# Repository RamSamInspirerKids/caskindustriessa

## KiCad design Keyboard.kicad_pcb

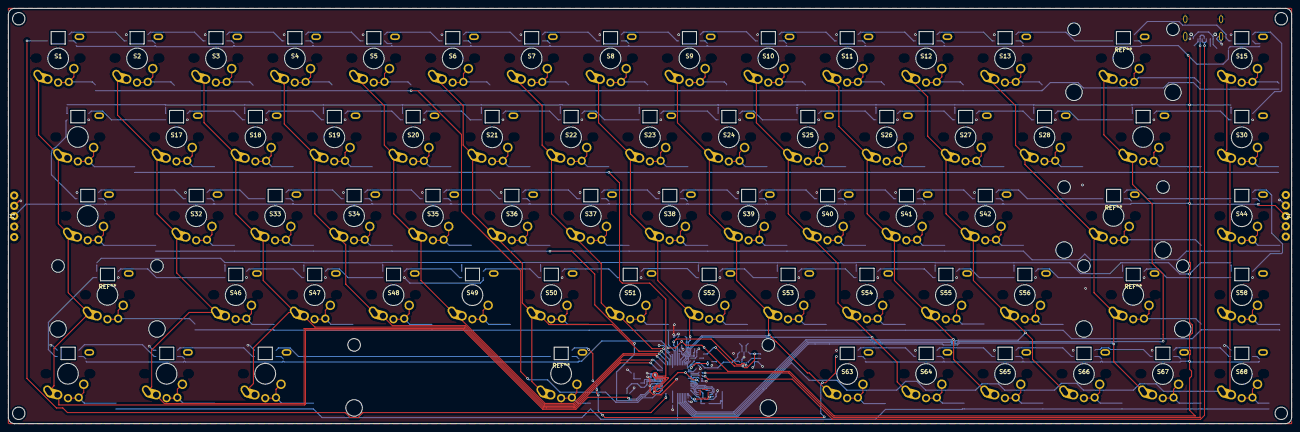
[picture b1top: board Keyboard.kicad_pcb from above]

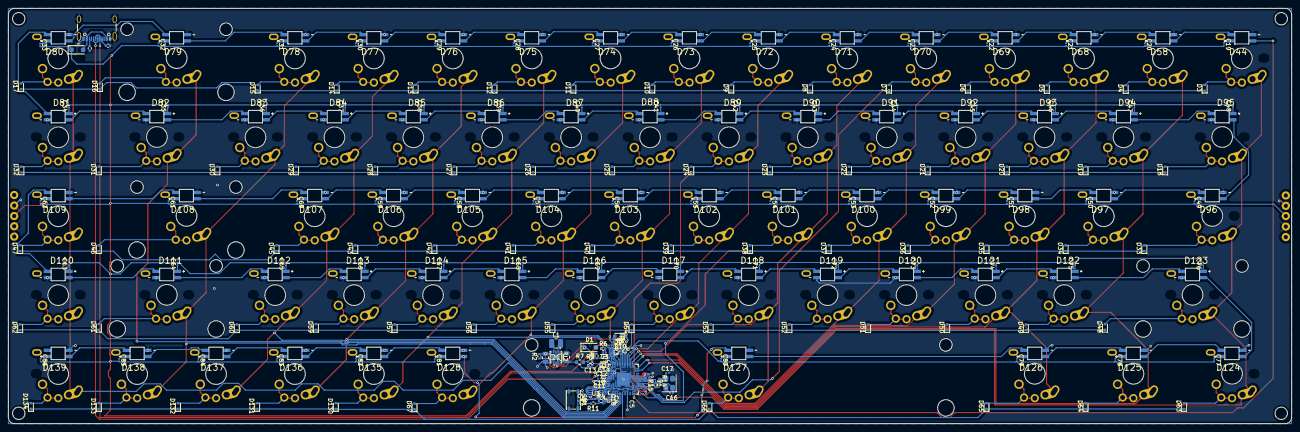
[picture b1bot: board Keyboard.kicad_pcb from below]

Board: 2 copper layers, 309.8 x 100.2 mm, 320 parts (250 on the bottom side), 257 nets.

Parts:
C1, C2: 47u; C_0805_2012Metric
C3: 1n; C_0201_0603Metric
C4, C5, C6, C7, C8, C9, C10, C11, C15: 100n; C_0201_0603Metric
C12, C13, C14, C18: 2u2; C_0402_1005Metric
C16, C17: 15p; C_0201_0603Metric
C19, C20, C21, C22, C23, C24, C25, C26, C27, C28, C29, C30, C31, C32, C33, C34, C35, C36, C37, C38, C39, C40, C41, C42, C43, C44, C45, C46, C47, C48, C49, C50, C51, C52, C53, C54, C55, C56, C57, C58, C59, C60, C61, C62, C63, C64, C65, C66, C67, C68, C69, C70, C71, C72, C73, C74, C75, C76, C77, C78, C79, C80, C81, C82, C83, C84, C85, C86: C0603X5R1A104M030BC; C_0201_0603Metric
D1, D129: MBR1020VL_R1_00001; D_SOD-123F
D2: LTST-C191KGKT; LED_0603_1608Metric
D3, D4, D5, D6, D7, D8, D9, D10, D11, D12, D13, D14, D15, D16, D17, D18, D19, D20, D21, D22, D23, D24, D25, D26, D27, D28, D29, D30, D31, D32, D33, D34, D35, D36, D37, D38, D39, D40, D41, D42, D43, D45, D46, D47, D48, D49, D50, D51, D52, D53, D54, D55, D56, D57, D59, D60, D61, D62, D63, D64, D65, D66, D67, D130, D131, D132, D133, D134: Diode; D_SOD-523
D44, D58, D68, D69, D70, D71, D72, D73, D74, D75, D76, D77, D78, D79, D80, D81, D82, D83, D84, D85, D86, D87, D88, D89, D90, D91, D92, D93, D94, D95, D96, D97, D98, D99, D100, D101, D102, D103, D104, D105, D106, D107, D108, D109, D110, D111, D112, D113, D114, D115, D116, D117, D118, D119, D120, D121, D122, D123, D124, D125, D126, D127, D128, D135, D136, D137, D138, D139: SK6812-E; LED_SK6812-E
J1, J4: Conn_01x05_Socket; Female Connector Pogo 5
J3: USB_C_Receptacle_USB2.0_16P; USB_C_Receptacle_GCT_USB4105-xx-A_16P_TopMnt_Horizontal
L1: SRN2512-2R2M; L_1008_2520Metric
Q1: DMG1012T-7; SOT-523
R1: 10k; R_0402_1005Metric
R2, R6, R8: 100k; R_0402_1005Metric
R3: 470R; R_0402_1005Metric
R4, R15: NO-FIT; R_0402_1005Metric
R5: 200k; R_0402_1005Metric
R7: 200R; R_0603_1608Metric
R9: 1R; R_0402_1005Metric
R10: 5k6; R_0402_1005Metric
R11, R14: 1k; R_0402_1005Metric
R12, R13: 27R; R_0201_0603Metric
R16, R17: 5k1; R_0402_1005Metric
S1, S2, S3, S4, S5, S6, S7, S8, S9, S10, S11, S12, S13, S15, S17, S18, S19, S20, S21, S22, S23, S24, S25, S26, S27, S28, S30, S32, S33, S34, S35, S36, S37, S38, S39, S40, S41, S42, S44, S46, S47, S48, S49, S50, S51, S52, S53, S54, S55, S56, S58, S63, S64, S65, S66, S67, S68: Keyswitch; 1.00U Keyswitch
S14: Keyswitch; 2.00U Keyswitch
S16, S29: Keyswitch; 1.50U Keyswitch
S31, S57: Keyswitch; 1.75U Keyswitch
S43, S45: Keyswitch; 2.25U Keyswitch
S59, S60, S61: Keyswitch; 1.25U Keyswitch
S62: Keyswitch; 6.25U Keyswitch
SW1: PTS810 SJK 250 SMTR LFS; SW_SPST_PTS810
U1: RP2040; QFN-56-1EP_7x7mm_P0.4mm_EP3.2x3.2mm
U2: RT6150B-33GQW; DFN-10-1EP_2.6x2.6mm_P0.5mm_EP1.3x2.2mm
U3: W25Q16JVUXIQ; SON50P300X200X60-9N
Y1: ECS-120-8-33-JGN-TR; Crystal_SMD_SeikoEpson_FA238-4Pin_3.2x2.5mm

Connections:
+1V1: C9.1, C11.1, C12.1, U1.23 (DVDD), U1.45 (VREG_VOUT), U1.50 (DVDD)
+3V3: C2.1, C4.1, C5.1, C6.1, C7.1, C8.1, C10.1, C14.1, C15.1, C18.1, Q1.1 (G), R4.2, R7.1, U1.1 (IOVDD), U1.10 (IOVDD), U1.22 (IOVDD), U1.33 (IOVDD), U1.42 (IOVDD), U1.44 (VREG_IN), U1.48 (USB_VDD), U1.49 (IOVDD), U2.1 (VOUT), U2.10 (FB), U3.8 (VCC)
/3V3_EN: R2.1, U2.6 (EN)
/RP2040/USB_DMX: R13.2, U1.46 (USB_DM)
/RP2040/USB_DPX: R12.2, U1.47 (USB_DP)
/XR: C17.1, R14.1, Y1.3
ADC_AVDD: C13.1, R9.2, U1.43 (ADC_AVDD)
ADC_VREF: R7.2, R9.1
GND: C1.2, C2.2, C3.2, C4.2, C5.2, C6.2, C7.2, C8.2, C9.2, C10.2, C11.2, C12.2, C13.2, C14.2, C15.2, C16.2, C17.2, C18.2, D2.1 (K), D44.3 (GND), D58.3 (GND), D68.3 (GND), D69.3 (GND), D70.3 (GND), D71.3 (GND), D72.3 (GND), D73.3 (GND), D74.3 (GND), D75.3 (GND), D76.3 (GND), D77.3 (GND), D78.3 (GND), D79.3 (GND), D80.3 (GND), D81.3 (GND), D82.3 (GND), D83.3 (GND), D84.3 (GND), D85.3 (GND), D86.3 (GND), D87.3 (GND), D88.3 (GND), D89.3 (GND), D90.3 (GND), D91.3 (GND), D92.3 (GND), D93.3 (GND), D94.3 (GND), D95.3 (GND), D96.3 (GND), D97.3 (GND), D98.3 (GND), D99.3 (GND), D100.3 (GND), D101.3 (GND), D102.3 (GND), D103.3 (GND), D104.3 (GND), D105.3 (GND), D106.3 (GND), D107.3 (GND), D108.3 (GND), D109.3 (GND), D110.3 (GND), D111.3 (GND), D112.3 (GND), D113.3 (GND), D114.3 (GND), D115.3 (GND), D116.3 (GND), D117.3 (GND), D118.3 (GND), D119.3 (GND), D120.3 (GND), D121.3 (GND), D122.3 (GND), D123.3 (GND), D124.3 (GND), D125.3 (GND), D126.3 (GND), D127.3 (GND), D128.3 (GND), D135.3 (GND), D136.3 (GND), D137.3 (GND), D138.3 (GND), D139.3 (GND), J1.2, J1.4, J3.A1 (GND), J3.A12 (GND), J3.B1 (GND), J3.B12 (GND), J3.S1 (SHIELD), J4.2, J4.4, R1.1, R6.1, R8.2, R16.2, R17.2, SW1.2 (B), U1.19 (TESTEN), U1.57 (GND), U2.3 (GND), U2.9 (GND), U2.11 (EXP), U3.4 (GND), Y1.2, Y1.4
GPIO0: S11.1, S26.1, S41.1, S55.1, S65.1, U1.2 (GPIO0)
GPIO1: S12.1, S27.1, S42.1, S56.1, S66.1, U1.3 (GPIO1)
GPIO2: S14.1, S29.1, U1.4 (GPIO2)
GPIO3: S13.1, S28.1, S43.1, S57.1, S67.1, U1.5 (GPIO3)
GPIO4: S15.1, S30.1, S44.1, S58.1, S68.1, U1.6 (GPIO4)
GPIO5: D63.1 (K), D64.1 (K), D65.1 (K), D66.1 (K), D67.1 (K), D130.1 (K), D131.1 (K), D132.1 (K), D133.1 (K), D134.1 (K), U1.7 (GPIO5)
GPIO11: D44.4 (DIN), U1.14 (GPIO11)
GPIO12: D3.1 (K), D4.1 (K), D5.1 (K), D6.1 (K), D7.1 (K), D8.1 (K), D9.1 (K), D10.1 (K), D11.1 (K), D12.1 (K), D13.1 (K), D14.1 (K), D15.1 (K), D16.1 (K), D17.1 (K), U1.15 (GPIO12)
GPIO13: D18.1 (K), D19.1 (K), D20.1 (K), D21.1 (K), D22.1 (K), D23.1 (K), D24.1 (K), D25.1 (K), D26.1 (K), D27.1 (K), D28.1 (K), D29.1 (K), D30.1 (K), D31.1 (K), D32.1 (K), U1.16 (GPIO13)
GPIO14: D33.1 (K), D34.1 (K), D35.1 (K), D36.1 (K), D37.1 (K), D38.1 (K), D39.1 (K), D40.1 (K), D41.1 (K), D42.1 (K), D43.1 (K), D45.1 (K), D46.1 (K), D47.1 (K), U1.17 (GPIO14)
GPIO15: S1.1, S16.1, S31.1, S45.1, S59.1, U1.18 (GPIO15)
GPIO16: S2.1, S17.1, S32.1, S46.1, S60.1, U1.27 (GPIO16)
GPIO17: S3.1, S18.1, S33.1, S47.1, S61.1, U1.28 (GPIO17)
GPIO18: S4.1, S19.1, S34.1, S48.1, U1.29 (GPIO18)
GPIO19: S5.1, S20.1, S35.1, S49.1, U1.30 (GPIO19)
GPIO20: S6.1, S21.1, S36.1, S50.1, S62.1, U1.31 (GPIO20)
GPIO21: S7.1, S22.1, S37.1, S51.1, U1.32 (GPIO21)
GPIO22: D48.1 (K), D49.1 (K), D50.1 (K), D51.1 (K), D52.1 (K), D53.1 (K), D54.1 (K), D55.1 (K), D56.1 (K), D57.1 (K), D59.1 (K), D60.1 (K), D61.1 (K), D62.1 (K), U1.34 (GPIO22)
GPIO23: R8.1, U1.35 (GPIO23), U2.7 (PS)
GPIO24: R1.2, R10.1, U1.36 (GPIO24)
GPIO25: R3.1, U1.37 (GPIO25)
GPIO26_ADC0: S8.1, S23.1, S38.1, S52.1, U1.38 (GPIO26_ADC0)
GPIO27_ADC1: S9.1, S24.1, S39.1, S53.1, S63.1, U1.39 (GPIO27_ADC1)
GPIO28_ADC2: S10.1, S25.1, S40.1, S54.1, S64.1, U1.40 (GPIO28_ADC2)
GPIO29_ADC3: C3.1, Q1.2 (S), R6.2, U1.41 (GPIO29_ADC3)
unnamed: D2.2 (A), R3.2
unnamed: D3.2 (A), S1.2
unnamed: D4.2 (A), S2.2
unnamed: D5.2 (A), S3.2
unnamed: D6.2 (A), S4.2
unnamed: D7.2 (A), S5.2
unnamed: D8.2 (A), S6.2
unnamed: D9.2 (A), S7.2
unnamed: D10.2 (A), S8.2
unnamed: D11.2 (A), S9.2
unnamed: D12.2 (A), S10.2
unnamed: D13.2 (A), S11.2
unnamed: D14.2 (A), S12.2
unnamed: D15.2 (A), S13.2
unnamed: D16.2 (A), S14.2
unnamed: D17.2 (A), S15.2
unnamed: D18.2 (A), S16.2
unnamed: D19.2 (A), S17.2
unnamed: D20.2 (A), S18.2
unnamed: D21.2 (A), S19.2
unnamed: D22.2 (A), S20.2
unnamed: D23.2 (A), S21.2
unnamed: D24.2 (A), S22.2
unnamed: D25.2 (A), S23.2
unnamed: D26.2 (A), S24.2
unnamed: D27.2 (A), S25.2
unnamed: D28.2 (A), S26.2
unnamed: D29.2 (A), S27.2
unnamed: D30.2 (A), S28.2
unnamed: D31.2 (A), S29.2
unnamed: D32.2 (A), S30.2
unnamed: D33.2 (A), S31.2
unnamed: D34.2 (A), S32.2
unnamed: D35.2 (A), S33.2
unnamed: D36.2 (A), S34.2
unnamed: D37.2 (A), S35.2
unnamed: D38.2 (A), S36.2
unnamed: D39.2 (A), S37.2
unnamed: D40.2 (A), S38.2
unnamed: D41.2 (A), S39.2
unnamed: D42.2 (A), S40.2
unnamed: D43.2 (A), S41.2
unnamed: D44.2 (DOUT), D58.4 (DIN)
unnamed: C19.1, D44.1 (VDD)
unnamed: D45.2 (A), S42.2
unnamed: D46.2 (A), S43.2
unnamed: D47.2 (A), S44.2
unnamed: D48.2 (A), S45.2
unnamed: D49.2 (A), S46.2
unnamed: D50.2 (A), S47.2
unnamed: D51.2 (A), S48.2
unnamed: D52.2 (A), S49.2
unnamed: D53.2 (A), S50.2
unnamed: D54.2 (A), S51.2
unnamed: D55.2 (A), S52.2
unnamed: D56.2 (A), S53.2
unnamed: D57.2 (A), S54.2
unnamed: D58.2 (DOUT), D68.4 (DIN)
unnamed: C20.1, D58.1 (VDD)
unnamed: D59.2 (A), S55.2
unnamed: D60.2 (A), S56.2
unnamed: D61.2 (A), S57.2
unnamed: D62.2 (A), S58.2
unnamed: D63.2 (A), S59.2
unnamed: D64.2 (A), S60.2
unnamed: D65.2 (A), S61.2
unnamed: D66.2 (A), S62.2
unnamed: D67.2 (A), S63.2
unnamed: D68.2 (DOUT), D69.4 (DIN)
unnamed: C21.1, D68.1 (VDD)
unnamed: D69.2 (DOUT), D70.4 (DIN)
unnamed: C22.1, D69.1 (VDD)
unnamed: D70.2 (DOUT), D71.4 (DIN)
unnamed: C23.1, D70.1 (VDD)
unnamed: D71.2 (DOUT), D72.4 (DIN)
unnamed: C24.1, D71.1 (VDD)
unnamed: D72.2 (DOUT), D73.4 (DIN)
unnamed: C25.1, D72.1 (VDD)
unnamed: D73.2 (DOUT), D74.4 (DIN)
unnamed: C26.1, D73.1 (VDD)
unnamed: D74.2 (DOUT), D75.4 (DIN)
unnamed: C27.1, D74.1 (VDD)
unnamed: D75.2 (DOUT), D76.4 (DIN)
unnamed: C28.1, D75.1 (VDD)
unnamed: D76.2 (DOUT), D77.4 (DIN)
unnamed: C29.1, D76.1 (VDD)
unnamed: D77.2 (DOUT), D78.4 (DIN)
unnamed: C30.1, D77.1 (VDD)
unnamed: D78.2 (DOUT), D79.4 (DIN)
unnamed: C31.1, D78.1 (VDD)
unnamed: D79.2 (DOUT), D80.4 (DIN)
unnamed: C32.1, D79.1 (VDD)
unnamed: D80.2 (DOUT), D81.4 (DIN)
unnamed: C33.1, D80.1 (VDD)
unnamed: D81.2 (DOUT), D82.4 (DIN)
unnamed: C34.1, D81.1 (VDD)
unnamed: D82.2 (DOUT), D83.4 (DIN)
unnamed: C35.1, D82.1 (VDD)
unnamed: D83.2 (DOUT), D84.4 (DIN)
unnamed: C36.1, D83.1 (VDD)
unnamed: D84.2 (DOUT), D85.4 (DIN)
unnamed: C37.1, D84.1 (VDD)
unnamed: D85.2 (DOUT), D86.4 (DIN)
unnamed: C38.1, D85.1 (VDD)
unnamed: D86.2 (DOUT), D87.4 (DIN)
unnamed: C39.1, D86.1 (VDD)
unnamed: D87.2 (DOUT), D88.4 (DIN)
unnamed: C40.1, D87.1 (VDD)
unnamed: D88.2 (DOUT), D89.4 (DIN)
unnamed: C41.1, D88.1 (VDD)
unnamed: D89.2 (DOUT), D90.4 (DIN)
unnamed: C42.1, D89.1 (VDD)
unnamed: D90.2 (DOUT), D91.4 (DIN)
unnamed: C43.1, D90.1 (VDD)
unnamed: D91.2 (DOUT), D92.4 (DIN)
unnamed: C44.1, D91.1 (VDD)
unnamed: D92.2 (DOUT), D93.4 (DIN)
unnamed: C45.1, D92.1 (VDD)
unnamed: D93.2 (DOUT), D94.4 (DIN)
unnamed: C46.1, D93.1 (VDD)
unnamed: D94.2 (DOUT), D95.4 (DIN)
unnamed: C47.1, D94.1 (VDD)
unnamed: D95.2 (DOUT), D96.4 (DIN)
unnamed: C48.1, D95.1 (VDD)
unnamed: D96.2 (DOUT), D97.4 (DIN)
unnamed: C49.1, D96.1 (VDD)
unnamed: D97.2 (DOUT), D98.4 (DIN)
unnamed: C50.1, D97.1 (VDD)
unnamed: D98.2 (DOUT), D99.4 (DIN)
unnamed: C51.1, D98.1 (VDD)
unnamed: C52.1, D99.1 (VDD)
unnamed: D99.2 (DOUT), D100.4 (DIN)
unnamed: D100.2 (DOUT), D101.4 (DIN)
unnamed: C53.1, D100.1 (VDD)
unnamed: D101.2 (DOUT), D102.4 (DIN)
unnamed: C54.1, D101.1 (VDD)
unnamed: D102.2 (DOUT), D103.4 (DIN)
unnamed: C55.1, D102.1 (VDD)
unnamed: D103.2 (DOUT), D104.4 (DIN)
unnamed: C56.1, D103.1 (VDD)
unnamed: D104.2 (DOUT), D105.4 (DIN)
unnamed: C57.1, D104.1 (VDD)
unnamed: D105.2 (DOUT), D106.4 (DIN)
unnamed: C58.1, D105.1 (VDD)
unnamed: D106.2 (DOUT), D107.4 (DIN)
unnamed: C59.1, D106.1 (VDD)
unnamed: D107.2 (DOUT), D108.4 (DIN)
unnamed: C60.1, D107.1 (VDD)
unnamed: D108.2 (DOUT), D109.4 (DIN)
unnamed: C61.1, D108.1 (VDD)
unnamed: D109.2 (DOUT), D110.4 (DIN)
unnamed: C62.1, D109.1 (VDD)
unnamed: D110.2 (DOUT), D111.4 (DIN)
unnamed: C63.1, D110.1 (VDD)
unnamed: D111.2 (DOUT), D112.4 (DIN)
unnamed: C64.1, D111.1 (VDD)
unnamed: D112.2 (DOUT), D113.4 (DIN)
unnamed: C65.1, D112.1 (VDD)
unnamed: D113.2 (DOUT), D114.4 (DIN)
unnamed: C66.1, D113.1 (VDD)
unnamed: D114.2 (DOUT), D115.4 (DIN)
unnamed: C67.1, D114.1 (VDD)
unnamed: D115.2 (DOUT), D116.4 (DIN)
unnamed: C68.1, D115.1 (VDD)
unnamed: D116.2 (DOUT), D117.4 (DIN)
unnamed: C69.1, D116.1 (VDD)
unnamed: D117.2 (DOUT), D118.4 (DIN)
unnamed: C70.1, D117.1 (VDD)
unnamed: D118.2 (DOUT), D119.4 (DIN)
unnamed: C71.1, D118.1 (VDD)
unnamed: D119.2 (DOUT), D120.4 (DIN)
unnamed: C72.1, D119.1 (VDD)
unnamed: D120.2 (DOUT), D121.4 (DIN)
unnamed: C73.1, D120.1 (VDD)
unnamed: D121.2 (DOUT), D122.4 (DIN)
unnamed: C74.1, D121.1 (VDD)
unnamed: D122.2 (DOUT), D123.4 (DIN)
unnamed: C75.1, D122.1 (VDD)
unnamed: D123.2 (DOUT), D124.4 (DIN)
unnamed: C76.1, D123.1 (VDD)
unnamed: D124.2 (DOUT), D125.4 (DIN)
unnamed: C77.1, D124.1 (VDD)
unnamed: D125.2 (DOUT), D126.4 (DIN)
unnamed: C78.1, D125.1 (VDD)
unnamed: D126.2 (DOUT), D127.4 (DIN)
unnamed: C79.1, D126.1 (VDD)
unnamed: D127.2 (DOUT), D128.4 (DIN)
unnamed: C80.1, D127.1 (VDD)
unnamed: D128.2 (DOUT), D135.4 (DIN)
unnamed: C81.1, D128.1 (VDD)
unnamed: D129.2 (A), J3.A4 (VBUS), J3.A9 (VBUS), J3.B4 (VBUS), J3.B9 (VBUS)
unnamed: D130.2 (A), S64.2
unnamed: D131.2 (A), S65.2
unnamed: D132.2 (A), S66.2
unnamed: D133.2 (A), S67.2
unnamed: D134.2 (A), S68.2
unnamed: D135.2 (DOUT), D136.4 (DIN)
unnamed: C82.1, D135.1 (VDD)
unnamed: D136.2 (DOUT), D137.4 (DIN)
unnamed: C83.1, D136.1 (VDD)
unnamed: D137.2 (DOUT), D138.4 (DIN)
unnamed: C84.1, D137.1 (VDD)
unnamed: D138.2 (DOUT), D139.4 (DIN)
unnamed: C85.1, D138.1 (VDD)
unnamed: C86.1, D139.1 (VDD)
unnamed: J3.A5 (CC1), R16.1
unnamed: J3.B5 (CC2), R17.1
unnamed: Q1.3 (D), R5.1
unnamed: R11.2, SW1.1 (A)
unnamed: L1.1, U2.4 (LX1)
unnamed: L1.2, U2.2 (LX2)
QSPI_SCLK: U1.52 (QSPI_SCLK), U3.6 (CLK)
QSPI_SD0: U1.53 (QSPI_SD0), U3.5 (DI_(IO0))
QSPI_SD1: U1.55 (QSPI_SD1), U3.2 (DO_(IO1))
QSPI_SD2: U1.54 (QSPI_SD2), U3.3 (~WP_(IO2))
QSPI_SD3: U1.51 (QSPI_SD3), U3.7 (~HOLD_OR_RESET_(IO3))
QSPI_SS: R4.1, R11.1, U1.56 (QSPI_SS), U3.1 (~CS)
USB_DM: J3.A7 (D-), J3.B7 (D-), R13.1
USB_DP: J3.A6 (D+), J3.B6 (D+), R12.1
VBUS: C19.2, C20.2, C21.2, C22.2, C23.2, C24.2, C25.2, C26.2, C27.2, C28.2, C29.2, C30.2, C31.2, C32.2, C33.2, C34.2, C35.2, C36.2, C37.2, C38.2, C39.2, C40.2, C41.2, C42.2, C43.2, C44.2, C45.2, C46.2, C47.2, C48.2, C49.2, C50.2, C51.2, C52.2, C53.2, C54.2, C55.2, C56.2, C57.2, C58.2, C59.2, C60.2, C61.2, C62.2, C63.2, C64.2, C65.2, C66.2, C67.2, C68.2, C69.2, C70.2, C71.2, C72.2, C73.2, C74.2, C75.2, C76.2, C77.2, C78.2, C79.2, C80.2, C81.2, C82.2, C83.2, C84.2, C85.2, C86.2, D1.2 (A), D129.1 (K), J1.3, J4.3, R10.2
VS: C1.1, D1.1 (K), R2.2, R5.2, U2.5 (VIN), U2.8 (VINA)
XIN: C16.1, R15.1, U1.20 (XIN), Y1.1
XOUT: R14.2, R15.2, U1.21 (XOUT)
